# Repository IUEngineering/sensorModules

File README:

In dit project wordt er aan een pH sensormodule gewerkt. Deze module kan draadloze de gemeten pH waardes verzenden.

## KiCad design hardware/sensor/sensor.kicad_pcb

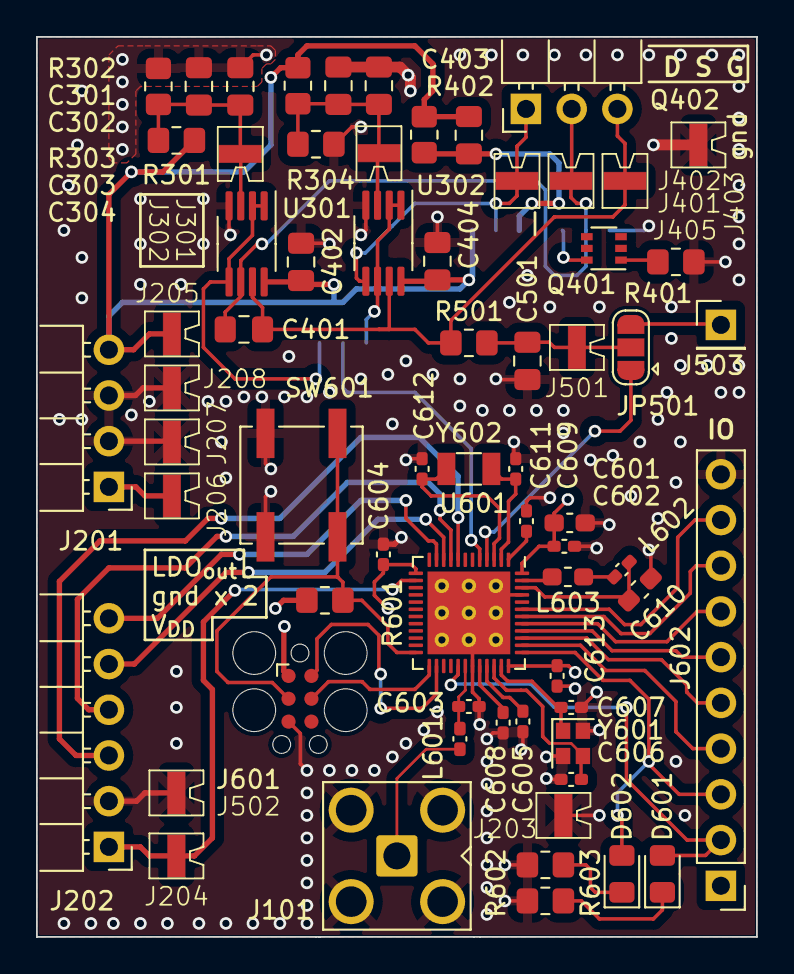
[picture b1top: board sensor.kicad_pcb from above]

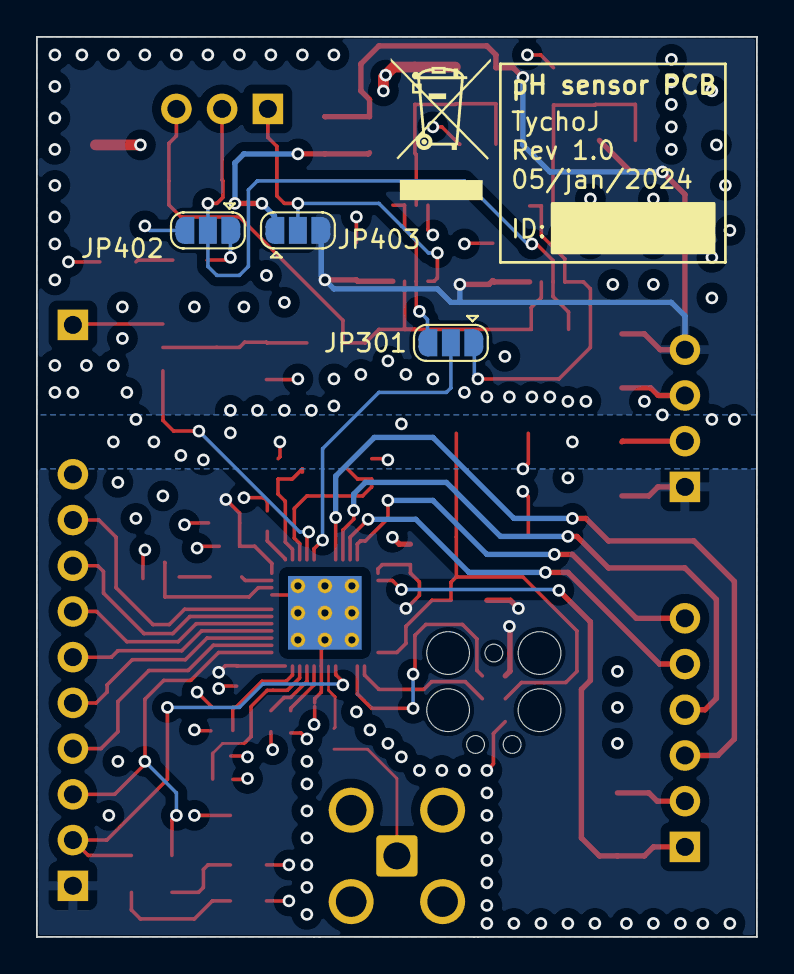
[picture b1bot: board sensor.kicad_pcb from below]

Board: 4 copper layers, 40.0 x 50.0 mm, 69 parts (3 on the bottom side), 47 nets.

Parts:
C301, C303, C402, C404: 100n; C_0805_2012Metric_Pad1.18x1.45mm_HandSolder
C302, C304, C403: 10u; C_0805_2012Metric_Pad1.18x1.45mm_HandSolder
C401: TBD; C_0805_2012Metric_Pad1.18x1.45mm_HandSolder
C501: 1u; C_0805_2012Metric_Pad1.18x1.45mm_HandSolder
C601: 4u7; C_0603_1608Metric_Pad1.08x0.95mm_HandSolder
C602, C604, C609, C613: 100n; C_0402_1005Metric_Pad0.74x0.62mm_HandSolder
C603: 0p8; C_0402_1005Metric_Pad0.74x0.62mm_HandSolder
C605: 100p; C_0402_1005Metric_Pad0.74x0.62mm_HandSolder
C606, C607, C611, C612: 12p; C_0402_1005Metric_Pad0.74x0.62mm_HandSolder
C608: DNP; C_0402_1005Metric_Pad0.74x0.62mm_HandSolder
C610: 1u; C_0603_1608Metric_Pad1.08x0.95mm_HandSolder
D601: RED; D_0805_2012Metric_Pad1.15x1.40mm_HandSolder
D602: GREEN; D_0805_2012Metric_Pad1.15x1.40mm_HandSolder
J101: Conn_Coaxial; SMA_Amphenol_901-143_Horizontal
J201: PWR; PinHeader_1x04_P2.54mm_Horizontal
J202: control signals; PinHeader_1x06_P2.54mm_Horizontal
J203, J207, J208, J403, J502: GND; Testpoint_519xTR
J204: LDO_{EN}; Testpoint_519xTR
J205: V_{DD}AN; Testpoint_519xTR
J206: V_{DD}MCU; Testpoint_519xTR
J301, J302: U_{ref}; Testpoint_519xTR
J401: U_{SS}; Testpoint_519xTR
J402: U_{DD}; Testpoint_519xTR
J405: Out; Testpoint_519xTR
J501: ADC; Testpoint_519xTR
J503: toDefboard; PinHeader_1x01_P2.54mm_Vertical
J601: ISP; Tag-Connect_TC2030-IDC-FP_2x03_P1.27mm_Vertical
J602: IO; PinHeader_1x10_P2.54mm_Vertical
JP301, JP402, JP403: J|T; SolderJumper-3_P1.3mm_Open_RoundedPad1.0x1.5mm
JP501: SolderJumper_3_Open; SolderJumper-3_P1.3mm_Open_RoundedPad1.0x1.5mm
L601: 3n9; L_0402_1005Metric_Pad0.77x0.64mm_HandSolder
L602: 15n; L_0402_1005Metric_Pad0.77x0.64mm_HandSolder
L603: 10u; L_0603_1608Metric_Pad1.05x0.95mm_HandSolder
Q401: BC847BDW1; SOT-363_SC-70-6
Q402: NMOS; PinHeader_1x03_P2.54mm_Horizontal
R301, R302, R303, R304: R; R_0805_2012Metric_Pad1.20x1.40mm_HandSolder
R401: 4k7; R_0805_2012Metric_Pad1.20x1.40mm_HandSolder
R402: 56k; R_0805_2012Metric_Pad1.20x1.40mm_HandSolder
R501: 11k; R_0805_2012Metric_Pad1.20x1.40mm_HandSolder
R601: 18k; R_0805_2012Metric_Pad1.20x1.40mm_HandSolder
R602, R603: 5k1; R_0805_2012Metric_Pad1.20x1.40mm_HandSolder
SW601: SW_Push; SW_SPST_B3SL-1002P
U301, U302: LTC2064; MSOP-8_3x3mm_P0.65mm
U601: nRF52810-QFxx; QFN-48-1EP_6x6mm_P0.4mm_EP4.6x4.6mm_ThermalVias
Y601: Crystal_GND24; Crystal_SMD_2016-4Pin_2.0x1.6mm
Y602: Crystal; Crystal_SMD_3215-2Pin_3.2x1.5mm

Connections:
/Filter/In: C401.1, J405.1, Q402.3 (G), R501.1, U301.7, U302.7
/Filter/Out: JP501.1 (A), U601.4 (P0.02/AIN0)
/Microcontroller/LDO_{EN}: J202.1, J204.1, U601.14 (P0.11)
/Microcontroller/V_{DD}: C601.1, C602.1, C604.1, C613.1, J201.1, J206.1, J601.1, J602.1, R601.1, U601.13 (VDD), U601.36 (VDD), U601.48 (VDD)
/Microcontroller/V_{ref}: JP301.2 (C), U601.5 (P0.03/AIN1)
/Microcontroller/dcdc_dec4: C610.1, L602.1, U601.46 (DEC4)
/Microcontroller/io_p024: D601.2 (A), J602.2, U601.29 (P0.24)
/Microcontroller/io_p025: D602.2 (A), J602.3, U601.37 (P0.25)
/Microcontroller/io_p026: J602.4, U601.38 (P0.26)
/Microcontroller/io_p027: J602.5, U601.39 (P0.27)
/Microcontroller/io_p028: J602.6, U601.40 (P0.28/AIN4)
/Microcontroller/io_p029: J602.7, U601.41 (P0.29/AIN5)
/Microcontroller/io_p030: J602.8, U601.42 (P0.30/AIN6)
/Microcontroller/io_p031: J602.9, U601.43 (P0.31/AIN7)
/Microcontroller/osc_xc1: C606.1, U601.34 (XC1), Y601.3
/Microcontroller/osc_xc2: C607.1, U601.35 (XC2), Y601.1
/Microcontroller/osc_xl1: C611.1, U601.2 (P0.00/XL1), Y602.2
/Microcontroller/osc_xl2: C612.1, U601.3 (P0.01/XL2), Y602.1
/Microcontroller/rf_ant: J101.1 (In), L601.1
/Microcontroller/rf_out: C603.1, L601.2, U601.30 (ANT)
/Microcontroller/swd_clk: J601.2, U601.26 (SWDIO)
/Microcontroller/swd_io: J601.4, U601.25 (SWDCLK)
/Microcontroller/swd_rst: J601.3, R601.2, SW601.2, U601.24 (P0.21/~RESET)
/P_{IN}/EH-ON: J202.4, U601.9 (P0.07)
/P_{IN}/HBO-MCU: J202.3, U601.8 (P0.06)
/P_{IN}/LDO_{OUT}: C402.1, C403.1, C404.1, J201.4, J205.1, JP403.3 (B), R301.1, R303.1, R402.1, U301.8 (V+), U302.8 (V+)
/P_{IN}/PWG-LDO: J202.6, U601.11 (P0.09)
/P_{IN}/PWG-Vout: J202.5, U601.10 (P0.08)
/Reference/ref_0v5: JP301.3 (B), U302.1, U302.2 (-), U302.6 (-)
/Reference/ref_1v1: JP301.1 (A), U301.1, U301.2 (-), U301.5 (+)
GND: C301.2, C302.2, C303.2, C304.2, C402.2, C404.2, C501.2, C601.2, C602.2, C603.2, C604.2, C605.2, C606.2, C607.2, C608.2, C609.2, C610.2, C611.2, C612.2, C613.2, J101.2 (Ext), J201.2, J201.3, J202.2, J203.1, J207.1, J208.1, J403.1, J502.1, J601.5, J602.10, JP402.3 (B), R302.2, R304.2, R401.2, R602.2, R603.2, SW601.1, U301.4 (V-), U302.4 (V-), U601.31 (VSS), U601.45 (VSS), U601.49 (VSS), Y601.2, Y601.4
unnamed: D601.1 (K), R603.1
unnamed: D602.1 (K), R602.1
unnamed: C303.1, C304.1, J301.1, R303.2, R304.1, U302.3 (+)
unnamed: C301.1, C302.1, J302.1, R301.2, R302.1, U301.3 (+)
unnamed: C401.2, J401.1, JP402.2 (C), Q402.2 (S), U301.6 (-)
unnamed: J402.1, JP403.2 (C), Q402.1 (D), U302.5 (+)
unnamed: C501.1, J501.1, JP501.2 (C), R501.2
unnamed: J503.1, JP501.3 (B)
unnamed: JP402.1 (A), Q401.6 (C1)
unnamed: C403.2, JP403.1 (A), R402.2
unnamed: L602.2, L603.1
unnamed: Q401.1 (E1), R401.1
unnamed: L603.2, U601.47 (DCC)
unnamed: C609.1, U601.1 (DEC1)
unnamed: C608.1, U601.32 (DEC2)
unnamed: C605.1, U601.33 (DEC3)

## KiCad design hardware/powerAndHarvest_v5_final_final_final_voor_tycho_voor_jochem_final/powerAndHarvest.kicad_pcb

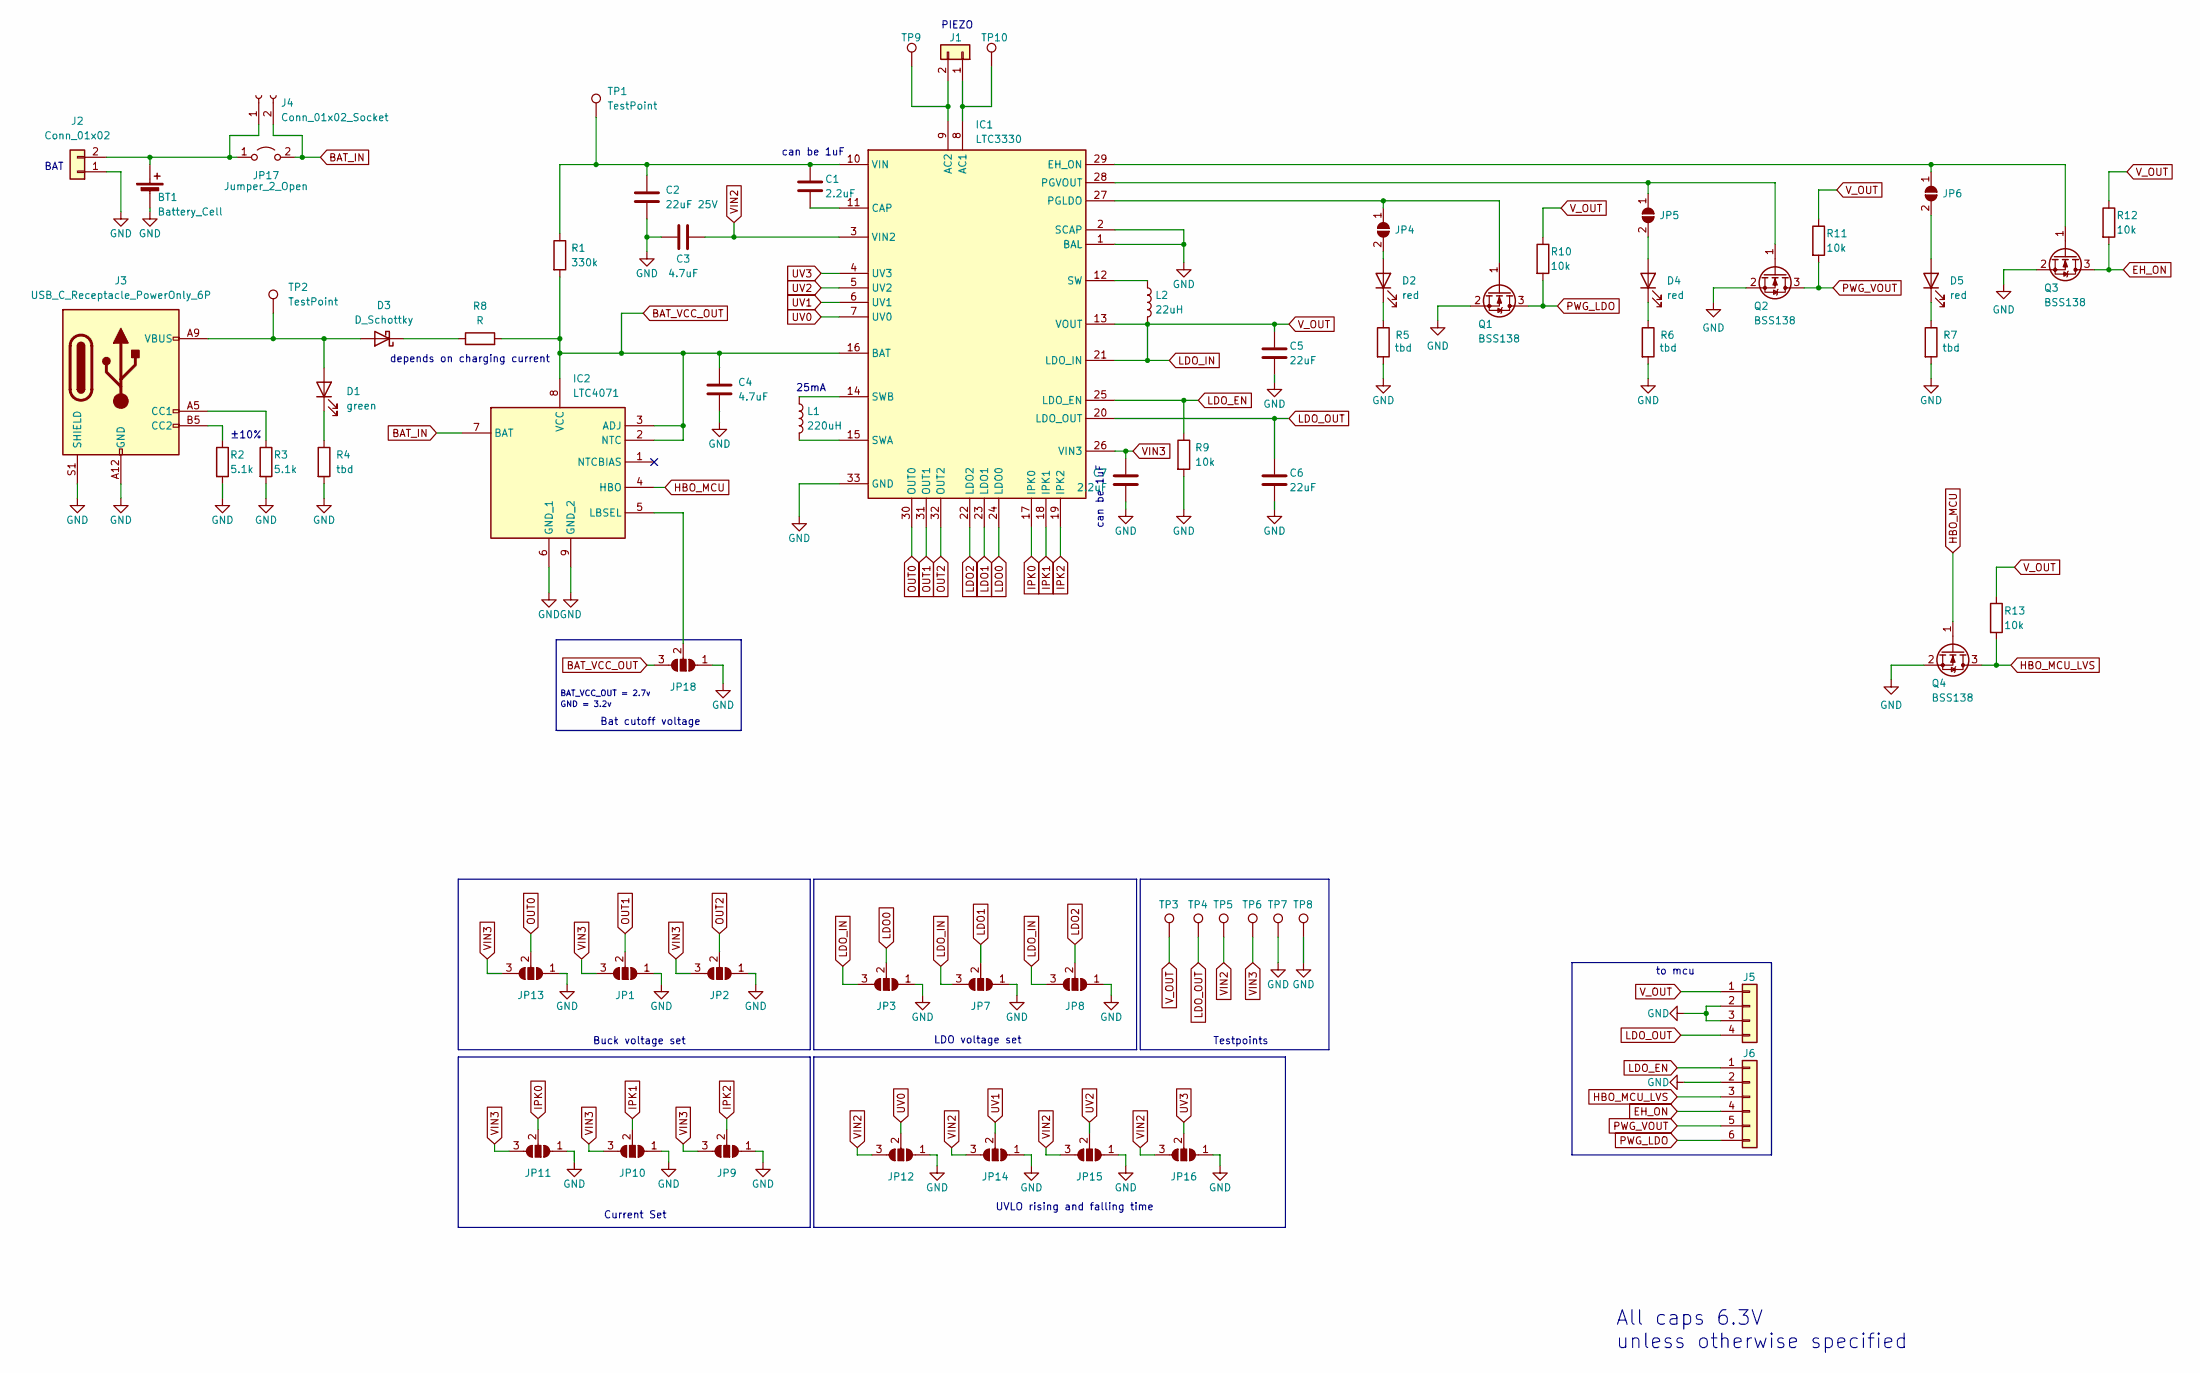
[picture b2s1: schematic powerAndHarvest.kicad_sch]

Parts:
BT1: Battery_Cell; BC-2404
C1, C7: 2.2uF; C_0805_2012Metric_Pad1.18x1.45mm_HandSolder
C2: 22uF 25V; C_1210_3225Metric_Pad1.33x2.70mm_HandSolder
C3, C4: 4.7uF; C_0805_2012Metric_Pad1.18x1.45mm_HandSolder
C5, C6: 22uF; C_0805_2012Metric_Pad1.18x1.45mm_HandSolder
D1: green; LED_0805_2012Metric_Pad1.15x1.40mm_HandSolder
D2, D4, D5: red; LED_0805_2012Metric_Pad1.15x1.40mm_HandSolder
D3: D_Schottky; D_SMF
IC1: LTC3330; QFN-32-1EP_5x5mm_P0.5mm_EP3.1x3.1mm_ThermalVias; Mouser Part Number 584-LTC3330EUH#PBF
IC2: LTC4071; MSOP-8-1EP_3x3mm_P0.65mm_EP1.5x1.8mm; Mouser Part Number 584-LTC4071EMS8E#PBF
J1: Conn_01x02; PhoenixContact_MC_1,5_2-G-3.81_1x02_P3.81mm_Horizontal
J2: Conn_01x02; Battery_pad_solder
J3: USB_C_Receptacle_PowerOnly_6P; USB4125-GF-A-0190
J4: Conn_01x02_Socket; Banana_Jack_2Pin
J5: Conn_01x04; PinSocket_1x04_P2.54mm_Horizontal
J6: Conn_01x06; PinSocket_1x06_P2.54mm_Horizontal
JP1, JP2, JP3, JP7, JP8, JP9, JP10, JP11, JP12, JP13, JP14, JP15, JP16, JP18: SolderJumper_3_Open; SolderJumper-3_P1.3mm_Open_RoundedPad1.0x1.5mm
JP4, JP5, JP6: SolderJumper_2_Open; SolderJumper-2_P1.3mm_Open_RoundedPad1.0x1.5mm
JP17: Jumper_2_Open; SolderJumper-2_P1.3mm_Open_RoundedPad1.0x1.5mm
L1: 220uH; L_Wuerth_WE-TPC-3816
L2: 22uH; L_Wuerth_WE-TPC-3816
Q1, Q2, Q3, Q4: BSS138; SOT-23
R1: 330k; R_0805_2012Metric_Pad1.20x1.40mm_HandSolder
R2, R3: 5.1k; R_0805_2012Metric_Pad1.20x1.40mm_HandSolder
R4, R5, R6, R7: tbd; R_0805_2012Metric_Pad1.20x1.40mm_HandSolder
R8: R; R_0805_2012Metric_Pad1.20x1.40mm_HandSolder
R9, R10, R11, R12, R13: 10k; R_0805_2012Metric_Pad1.20x1.40mm_HandSolder
TP1, TP2, TP3, TP4, TP5, TP6, TP7, TP8, TP9, TP10: TestPoint; Testpoint_519xTR

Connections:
BAT_IN: IC2.7 (BAT), J4.2, JP17.2 (B)
BAT_VCC_OUT: C4.1, IC1.16 (BAT), IC2.2 (NTC), IC2.3 (ADJ), IC2.8 (VCC), JP18.3 (B), R1.2, R8.2
EH_ON: J6.4, Q3.3 (D), R12.2
GND: BT1.2 (-), C2.2, C3.1, C4.2, C5.2, C6.2, C7.2, IC1.1 (BAL), IC1.2 (SCAP), IC1.33 (GND), IC2.6 (GND_1), IC2.9 (GND_2), J2.1, J3.A12 (GND), J3.B12 (GND), J3.S1 (SHIELD), J5.2, J5.3, J6.2, JP1.1 (A), JP2.1 (A), JP3.1 (A), JP7.1 (A), JP8.1 (A), JP9.1 (A), JP10.1 (A), JP11.1 (A), JP12.1 (A), JP13.1 (A), JP14.1 (A), JP15.1 (A), JP16.1 (A), JP18.1 (A), Q1.2 (S), Q2.2 (S), Q3.2 (S), Q4.2 (S), R2.2, R3.2, R4.2, R5.2, R6.2, R7.2, R9.2, TP7.1, TP8.1
HBO_MCU: IC2.4 (HBO), Q4.1 (G)
HBO_MCU_LVS: J6.3, Q4.3 (D), R13.2
IPK0: IC1.17 (IPK0), JP11.2 (C)
IPK1: IC1.18 (IPK1), JP10.2 (C)
IPK2: IC1.19 (IPK2), JP9.2 (C)
LDO0: IC1.24 (LDO0), JP3.2 (C)
LDO1: IC1.23 (LDO1), JP7.2 (C)
LDO2: IC1.22 (LDO2), JP8.2 (C)
LDO_EN: IC1.25 (LDO_EN), J6.1, R9.1
LDO_IN: C5.1, IC1.13 (VOUT), IC1.21 (LDO_IN), J5.1, JP3.3 (B), JP7.3 (B), JP8.3 (B), L2.2, R10.1, R11.1, R12.1, R13.1, TP3.1
LDO_OUT: C6.1, IC1.20 (LDO_OUT), J5.4, TP4.1
unnamed: BT1.1 (+), J2.2, J4.1, JP17.1 (A)
unnamed: D1.2 (A), D3.2 (A), J3.A9 (VBUS), J3.B9 (VBUS), TP2.1
unnamed: D1.1 (K), R4.1
unnamed: D2.2 (A), JP4.2 (B)
unnamed: D2.1 (K), R5.1
unnamed: D3.1 (K), R8.1
unnamed: D4.2 (A), JP5.2 (B)
unnamed: D4.1 (K), R6.1
unnamed: D5.2 (A), JP6.2 (B)
unnamed: D5.1 (K), R7.1
unnamed: IC1.8 (AC1), J1.1, TP10.1
unnamed: IC1.9 (AC2), J1.2, TP9.1
unnamed: C1.2, IC1.11 (CAP)
unnamed: IC1.29 (EH_ON), JP6.1 (A), Q3.1 (G)
unnamed: IC1.27 (PGLDO), JP4.1 (A), Q1.1 (G)
unnamed: IC1.28 (PGVOUT), JP5.1 (A), Q2.1 (G)
unnamed: IC1.12 (SW), L2.1
unnamed: IC1.15 (SWA), L1.2
unnamed: IC1.14 (SWB), L1.1
unnamed: C1.1, C2.1, IC1.10 (VIN), R1.1, TP1.1
unnamed: IC2.5 (LBSEL), JP18.2 (C)
unnamed: J3.A5 (CC1), R3.1
unnamed: J3.B5 (CC2), R2.1
OUT0: IC1.30 (OUT0), JP13.2 (C)
OUT1: IC1.31 (OUT1), JP1.2 (C)
OUT2: IC1.32 (OUT2), JP2.2 (C)
PWG_LDO: J6.6, Q1.3 (D), R10.2
PWG_VOUT: J6.5, Q2.3 (D), R11.2
UV0: IC1.7 (UV0), JP12.2 (C)
UV1: IC1.6 (UV1), JP14.2 (C)
UV2: IC1.5 (UV2), JP15.2 (C)
UV3: IC1.4 (UV3), JP16.2 (C)
VIN2: C3.2, IC1.3 (VIN2), JP12.3 (B), JP14.3 (B), JP15.3 (B), JP16.3 (B), TP5.1
VIN3: C7.1, IC1.26 (VIN3), JP1.3 (B), JP2.3 (B), JP9.3 (B), JP10.3 (B), JP11.3 (B), JP13.3 (B), TP6.1

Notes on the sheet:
All caps 6.3V unless otherwise specified
±10%
LDO voltage set
Bat cutoff voltage
25mA
Buck voltage set
BAT
depends on charging current
GND = 3.2v
BAT_VCC_OUT = 2.7v
can be 1uF
to mcu
Current Set
Testpoints
PIEZO
UVLO rising and falling time

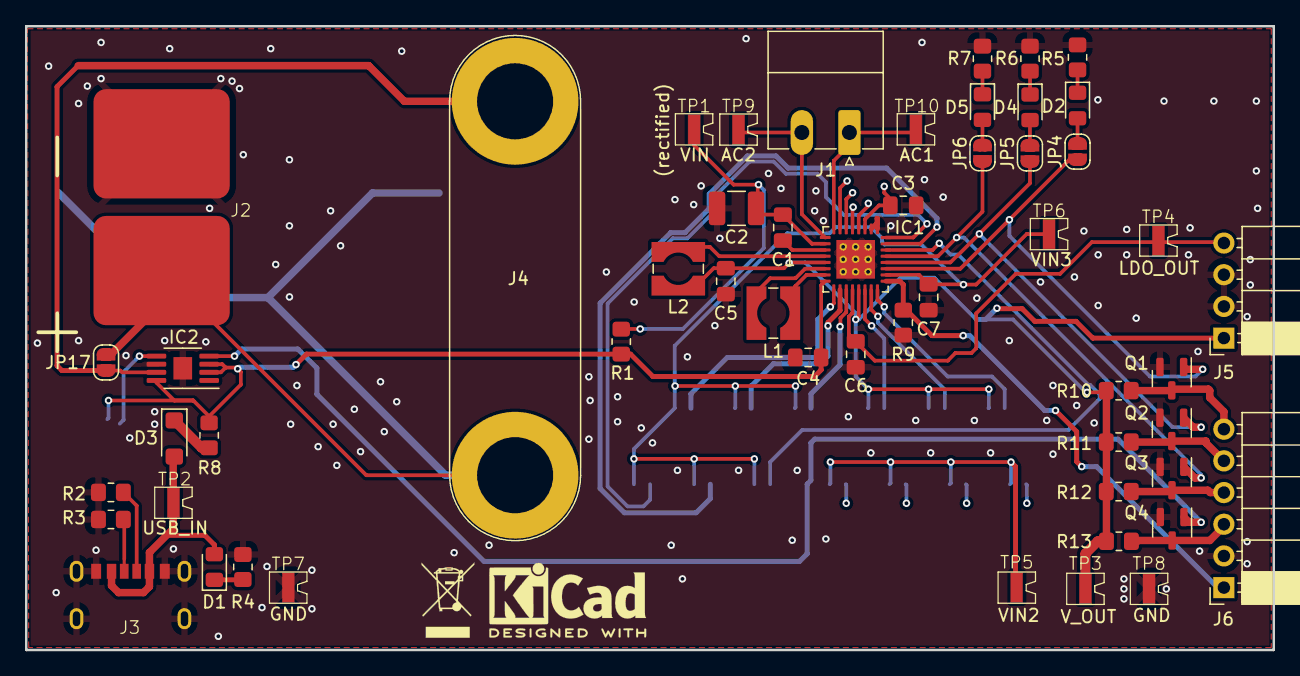
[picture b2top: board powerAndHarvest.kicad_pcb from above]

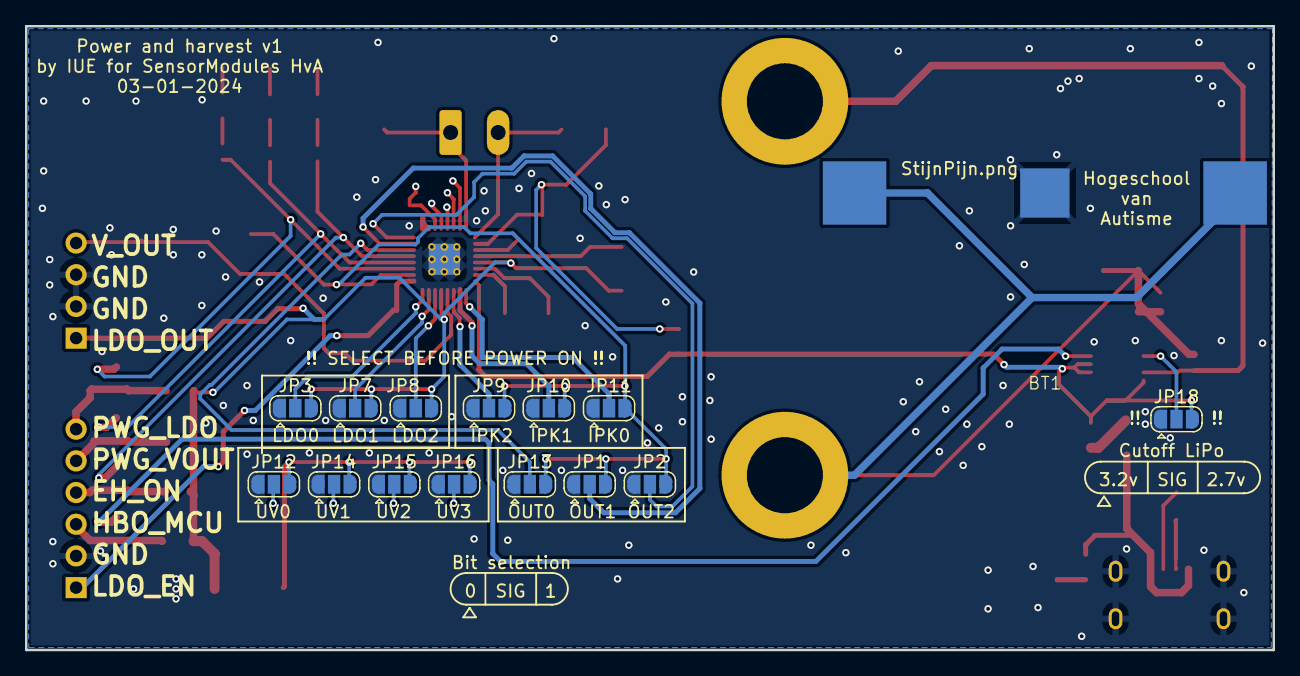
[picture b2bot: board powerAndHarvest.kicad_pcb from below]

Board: 4 copper layers, 100.0 x 50.0 mm, 68 parts (15 on the bottom side), 49 nets.

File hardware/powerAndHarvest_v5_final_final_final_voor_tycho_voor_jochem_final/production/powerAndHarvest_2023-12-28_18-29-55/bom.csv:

Designator,Footprint,Quantity,Value,LCSC Part #
BT1,BatteryHolder_ComfortableElectronic_CH273-2450_1x2450,1,Battery_Cell,
"C1, C7",0805,2,2.2uF,
C2,0805,1,22uF 25V,
"C3, C4",0805,2,4.7uF,
"C5, C6",0805,2,22uF,
D1,0805,1,green,
"D2, D4, D5",0805,3,red,
D3,D_SMF,1,D_Schottky,
IC1,QFN-32-1EP_5x5mm_P0.5mm_EP3.1x3.1mm_ThermalVias,1,LTC3330,
IC2,MSOP-8-1EP_3x3mm_P0.65mm_EP1.5x1.8mm,1,LTC4071,
J1,"PhoenixContact_MC_1,5_2-G-3.81_1x02_P3.81mm_Horizontal",1,Conn_01x02,
J2,Battery_pad_solder,1,Conn_01x02,
J3,USB_C_Receptacle_GCT_USB4125-xx-x_6P_TopMnt_Horizontal,1,USB_C_Receptacle_PowerOnly_6P,
J4,Banana_Jack_2Pin,1,Conn_01x02_Socket,
J5,PinHeader_1x04_P2.54mm_Horizontal,1,Conn_01x04,
J6,PinHeader_1x06_P2.54mm_Horizontal,1,Conn_01x06,
"JP1, JP10, JP11, JP12, JP13, JP14, JP15, JP16, JP18, JP2, JP3, JP7, JP8, JP9",SolderJumper-3_P1.3mm_Open_RoundedPad1.0x1.5mm,14,SolderJumper_3_Open,
JP17,SolderJumper-2_P1.3mm_Open_RoundedPad1.0x1.5mm,1,Jumper_2_Open,
"JP4, JP5, JP6",SolderJumper-2_P1.3mm_Open_RoundedPad1.0x1.5mm,3,SolderJumper_2_Open,
L1,L_Wuerth_WE-TPC-3816,1,220uH,
L2,L_Wuerth_WE-TPC-3816,1,22uH,
R1,0805,1,330k,
"R2, R3",0805,2,5.1k,
"R4, R5, R6, R7",0805,4,tbd,
R8,0805,1,R,
R9,0805,1,10k,
"TP1, TP10, TP2, TP3, TP4, TP5, TP6, TP7, TP8, TP9",Testpoint_519xTR,10,TestPoint,

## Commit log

2023-11-18 add readme
2023-11-18 Add initial report setup
2023-11-18 Remove unnecesairy comments
2023-11-20 Remove generated file from git
2023-11-20 Add setup for pathloss report
2023-11-20 Fix spelling mistake
2023-11-20 Add plan for contents
2023-11-22 Start work on the nRF module schematic
2023-11-22 Update gitignore for KiCad
2023-11-27 Add nrf52dkTestcode
2023-11-30 Add current work to git
2023-11-30 Add figure to help explain things
    This figure is not used at the moment in the report
2023-11-30 Add sections directory
2023-11-30 Fix latex table
2023-11-30 Add introduction and specifications
2023-11-30 Add raw format for the introduction
2023-12-08 Update specifications
    The reference electrode wasn't cable of handeling the previous pH range
2023-12-08 Add a begin of the device physics explenation
2023-12-11 Add functional decomp & specs
2023-12-11 added date
2023-12-11 Add some explenation about path loss and the two ray model
2023-12-11 remove blinkie
2023-12-11 Add RSS graph
2023-12-13 Add ISFETCircuit to report
2023-12-13 Add initial schematic
2023-12-18 Forgot what the changes were and I am to lazy to check them
2023-12-19 commit to save work from misbehaving laptop
2023-12-22 Write things about the filter
2023-12-22 Finish filter part for now
2023-12-22 Implement filter in KiCad
2024-01-03 Remove unused image
2024-01-03 Fix incorrect upstream
2024-01-03 Add part about the voltage divider
2024-01-05 Finished initial pcb routing
2024-01-05 Added WEEE symbol to the pcb
2024-01-05 Write words
2024-01-05 Changing some sentences
2024-01-08 Write more words
2024-01-08 Add finished PowerAndHarvest PCB
2024-01-08 Add bom and final version of rev 1.0
2024-01-11 Create todo list
2024-01-11 Add project for nRF
2024-01-11 Improve the introduction section
2024-01-11 Translate section titles from Englisch to Dutch
2024-01-11 Correct placement of square symbol of cosines
2024-01-12 Fix some spelling mistakes
2024-01-12 Write words about measuring the ISFET
2024-01-13 Fix placement of graph
2024-01-13 Add first version of methods section
2024-01-13 Add label for section methods
2024-01-13 Subsections are sections now
2024-01-13 Add more graphs
2024-01-13 Implement fixes proposed by Jochem
2024-01-13 Move to graphs from results to discussion
2024-01-14 Propose first final version of path loss report
2024-01-14 Fix warning in pathloss.tex
2024-01-14 Add appendix measurement report
2024-01-14 Write an arbitrary amount of words
2024-01-14 Add powerHarvest intro
2024-01-14 Place each section on it's own page
2024-01-14 Improve author name placement
2024-01-14 Add structure
2024-01-14 Fix / to \
2024-01-14 Remove appendix as section
2024-01-14 change specs to comply with probe abs values
2024-01-14 vorm verslag rode draad
2024-01-14 Add updates for specs, powerAndHarvest
2024-01-14 Write a ridiculous number of words
2024-01-14 Adjust filter values
2024-01-14 Adding ADC section
2024-01-14 Last changes before merge
2024-01-15 Final revision before handing in the report
2024-01-15 Add bibliography to table of contents
2024-01-15 Keep generated tex files for presentation out of the repo
2024-01-15 Creating initial presentation sections
2024-01-16 Start writing code
2024-01-16 Create somewhat working code
2024-01-16 some work for the presentation
2024-01-18 Program newest version of code This was during the oplevering.
2024-01-22 Adding the first presentation version
2024-01-22 Fixing mistake in the table
2024-01-22 Removing spec that follows from calculations later in the design
2024-01-22 Removing unnecessary subsections
2024-01-22 Write words about how the ISFET functions
2024-01-22 Add missing ADC block
2024-01-22 Write all kinds of words
2024-01-24 Write a whole bunch of words (you don't want to know man)
2024-01-25 Write an ordinary amount of words about testing
2024-01-26 Refactor all the things
2024-01-27 Write realisatie woorden
2024-01-27 Wrote initial version of rf design
2024-01-27 Finish realisatie partly
2024-01-27 Changing order of authors
2024-01-27 Sure write a large amount of words, oh boy!
2024-01-27 Replace all autoref with cref
2024-01-27 Change all values to \qty
2024-01-27 Fix Tycho mistake 😁
2024-01-27 Add serie numbers
2024-01-27 fix references
2024-01-28 Change location of text
2024-01-28 Write something about ADC loading effect
2024-01-28 Remove subsection methods from theoretisch kader
2024-01-28 Write something about the rf implementation
2024-01-28 dont remember
2024-01-28 reference to the specifications section for specifications
2024-01-28 Add text to remember specification
2024-01-28 Write test bs haha ok
2024-01-28 Change before merge
2024-01-28 Add introduction
2024-01-28 fix crap
2024-01-28 Remove shit
2024-01-28 Haha ok mooi
2024-01-28 Add specifications
2024-01-28 Voeg inleiding toe voor het hoofdstuk testen
2024-01-28 Change copyright year
2024-01-28 remove copyright
2024-01-28 Add changes to lots of shit
2024-01-28 Morged
2024-01-28 Haha samenvat :)
2024-01-28 Hha er waren probleem opsie!!
2024-01-28 haha ik vind eenden lief
2024-01-28 haha katten
2024-01-28 remove dumb file
2024-01-29 Add required images to the git
2024-01-29 hier is start van presentatie V2
2024-01-29 stagesss
2024-01-30 haha ik heb foto toegevoegd!! aan de presidentatie!!!! Obama
2024-01-30 Move peizo left
2024-01-30 Fucking move everything into the img folder because fuck moving files everytime that shit becomes a headache VERY fast lmao lol haha hihi hoho
2024-01-30 remove commented text
2024-01-30 Last push before switch to MPP
2024-01-30 Last push before MPP
2024-01-30 add place for rf
2024-01-30 Presentatie framework af haha katten UwU 🥺👉👈
2024-01-30 Add rf crap
2024-01-30 fix some random rf thing
2024-01-30 fixing some crap
2024-01-30 Some other stuff
2024-01-30 haha katten hoe hoe ik heb allemaal DINGEN GEDAAN!!!
2024-01-30 Add a few more dia's
2024-01-30 Energie Deel af
2024-01-30 Extra dia stompida
2024-01-30 Changed Sections
2024-01-30 fix positioning
2024-01-30 oefening 5001
2024-01-30 Add more end stuff in case of questions
2024-01-30 fix wrong photo, add RTOS vs baremetal
2024-01-30 Add last stuff
2024-01-31 Updateted
2024-01-31 kak vergeten
2024-04-13 Add actual description of the project
2024-04-13 Last update to the presentation
2024-04-13 Add files that should not be tracked
2024-04-13 integrate the appendix in the main report
2024-04-26 Start work on pH research chapter
2024-04-26 Change [ht] to [!htbp] for better figure and table placement
2024-04-27 add filter design order calculations
2024-04-28 Defined all the input specs of the AA-filter
2024-04-28 Write word
2024-04-28 add a bunch of files
2024-04-28 Fix power formula for filter
2024-04-29 Add labels and update equation filterCapMin
2024-04-29 Restructure and finish first version of filter implementation
2024-04-29 Add order graph
2024-04-29 Voeg uitleg over eisen kantelfrequentie toe
2024-04-29 Say something about the simulations
2024-04-29 Angepast om de tekst compleet te maken
2024-04-29 Do thing
2024-04-30 Add grid to referenceSimTrans graph
2024-04-30 Write thing
2024-04-30 Add cool block diagrams with circles hehe
2024-04-30 Add command for system output noise spec
2024-04-30 Change magic system noise spec number with command
2024-04-30 Add explanation for noise figures of basic signal blocks
2024-05-04 Add cool plot haha
2024-05-05 Add blinky as project structure
2024-05-05 Test ADC code
2024-05-09 Remove text with uninitialised information
2024-05-09 make the label a label of a chapter
2024-05-09 Extend the explanation about the noise requirements
2024-05-09 Make sure captions don't look like paragraphs
2024-05-09 Mark down part of the audio feedback
2024-05-09 give reference a better name
2024-05-09 Apply some of that feedback
2024-05-10 Do some of the things the feedback told me to do
2024-05-10 Do a lot of low and medium hanging fruit from the feedback Also expand the feedback document a little up to 30:45
2024-05-11 Fucking do all the things haha
2024-05-11 added explanation of isfet physics
2024-05-11 Sure write a bunch of bs!!!
2024-05-11 update the sources
2024-05-11 Fix dumb problem with pgfplots multiplication
2024-05-11 fix spelling
2024-05-12 remove incorrect amount of precision
2024-05-12 split text in smaller tex file
2024-05-12 place the temperature implementation section before the uC section
2024-05-12 make the label a label for a chapter
2024-05-12 Remove section introduction from subsection
2024-05-12 Added an introduction to the section
2024-05-12 Add missing label
2024-05-12 Adc test
2024-05-12 Fix Tycho bruh moments
2024-05-12 Update feedback file up to like 56 minutes.
2024-05-12 Fix the plots by adding like 20 different file types per plot lol
2024-05-12 some more text
2024-05-12 Fix simulation of voltage reference
2024-05-13 Remove the dumb synctex(busy) file
2024-05-13 Fix een heleboel test dingen
2024-05-13 Nog wat energy bs
2024-05-13 more text
2024-05-13 HAHAHA VERSLAGEN SCHRIJVEN IS ZO LEUK!!! IK VIND HET GEWELDIG!! jaaa joepie jeej ik wil nooit meer iets anders doen dan VERSLAGEN SCHRIJVEN!!! JAAdat vindIK ZO LEUK OM TE D!OEENN!!!!!
2024-05-13 add labels
2024-05-13 meer spanningsreferentie tekst
2024-05-13 add more text
2024-05-13 fix axis text
2024-05-14 Write a very small amount of words in the recommendations
2024-05-14 Finish recommendations
2024-05-14 Add more stuff
2024-05-14 Add more stuff...
2024-05-14 Laatste nullor
2024-05-14 Verbeter tekst over de implementatie van een temperatuurssensor
2024-05-14 Klaar met mcu en rf?
2024-05-14 Voeg te korte intro voeding toe
2024-05-14 commit before laptop die
2024-05-14 do stuff
2024-05-14 Finish disconcluvelingen
2024-05-14 meer tekst
2024-05-14 tekst analoog en comm pcb
2024-05-14 Add ignored file :(
2024-05-14 Replacement things hehe
